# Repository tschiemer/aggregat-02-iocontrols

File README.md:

# aggregat 02 IOControls PCB

User interface peripheral board.

For project info see: https://gitlab.zhdk.ch/aggregat-02/a01-firmware

https://gitlab.zhdk.ch/aggregat-02/a01-pcb-iocontrols

## License

This work is licensed under a Creative Commons Attribution 4.0 International License (CC BY 4.0)

## Revisions

### v1.2

- Replaced small footprint molex connectors with regular 1.00" pin headers.

### v1.1

- fixed not connected 3V3 between DIP switches
- fixed not connected button to GPIO line
- **BREAKING CHANGE** corrected CN3 connector pin assignment to fit with NUCLEO out connector (also see schematics)

## Bill of Materials

Number | Item | Cost per (10/100) Unit(s)  | Cost
--- | --- | --- | ---
1 | PCB Prototype (https://www.pcbway.com/) | 25.00* (10) | 2.50
1 | [DIP Switch SPST 8 Through Hole](https://www.digikey.ch/product-detail/en/78B08ST/GH7192-ND/726250) | 1.26 | 1.26
2 | [DIP Switch SPST 4 Through Hole](https://www.digikey.ch/product-detail/en/78B04T/GH7185-ND/726243) | 1.06 | 2.12
1 | 1 Pin header | |
1 | 2 Pin header 1.00" |  |
2 | 15 Pin header 1.00" |  |
8 | [SMD Res 270Ohm 1% 1/8W 0805 (2012 Metric)](https://www.digikey.ch/product-detail/en/CR0805-FX-2700ELF/118-CR0805-FX-2700ELFCT-ND/10673809) | 2.67 (100) | < 1.00
19 | [SMD Res 330Ohm 1% 1/8W 0805 (2012 Metric)](https://www.digikey.ch/product-detail/en/CRG0805F330R/A106061CT-ND/3477707) | 1.82 (100) | < 1.00
8 | [SMD Res 47kOhm 1% 1/8W 0805 (2012 Metric)](https://www.digikey.ch/product-detail/en/RC0805FR-0747KL/311-47.0KCRCT-ND/730920) |  1.49 (100) | < 1.00
27 | [SMD Res 100kOhm 1% 1/8W 0805 (2012 Metric)](https://www.digikey.ch/product-detail/en/RC0805FR-07100KL/311-100KCRCT-ND/730491) |  1.49 (100) | < 1.00
19| [SMD Cap 0.1uF 10% 6.3V 0805 (2012 Metric)](https://www.digikey.ch/product-detail/en/C0805C104K9RACTU/399-9155-6-ND/3523226) | 7.65 (100) | < 1.00
8 | [Bipolar (BJT) Transistor NPN 40V 800mA SOT-23-3](https://www.digikey.ch/product-detail/en/BSR14/BSR14CT-ND/965560) | 7.37 (100) | < 1.00
4 | Tactile switches |
8 | LEDs ~2 20mA | | ~2.00

* Delivery (~25.00) not included

Total material cost ~< 20.-

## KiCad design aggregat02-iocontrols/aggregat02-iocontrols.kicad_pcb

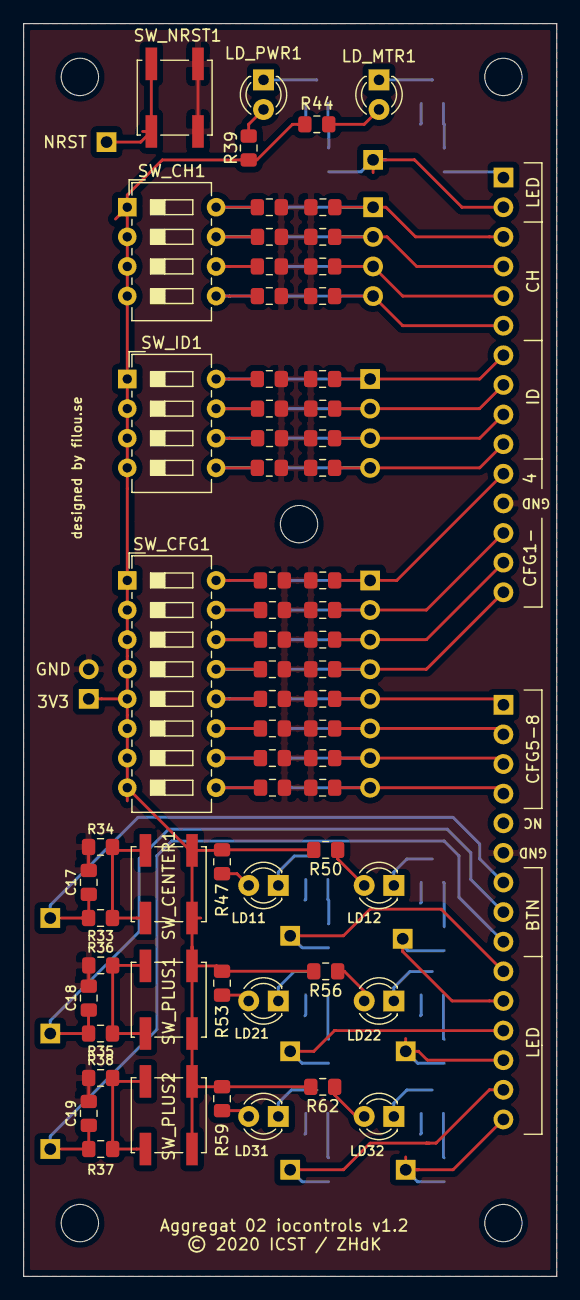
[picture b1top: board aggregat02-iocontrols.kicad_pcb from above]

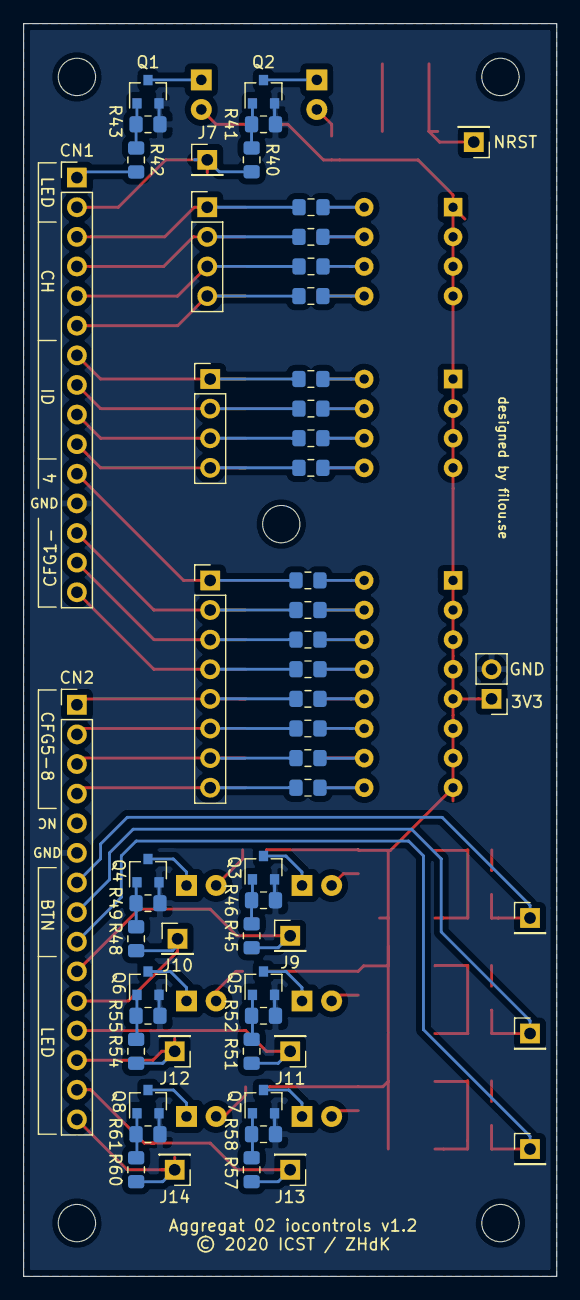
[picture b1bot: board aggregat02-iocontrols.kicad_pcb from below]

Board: 2 copper layers, 45.7 x 107.4 mm, 121 parts (57 on the bottom side), 73 nets.

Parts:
C1, C2, C3, C4, C5, C6, C7, C8, C9, C10, C11, C12, C13, C14, C15, C16, C17, C18, C19: C 0.1u 10% 6V3; C_0805_2012Metric_Pad1.15x1.40mm_HandSolder
CN1, CN2: Conn_01x15; PinHeader_1x15_P2.54mm_Vertical
J1, J2: Conn_01x04; PinHeader_1x04_P2.54mm_Vertical
J3: Conn_01x08; PinHeader_1x08_P2.54mm_Vertical
J4, J5, J6, J7, J9, J10, J11, J12, J13, J14: Conn_01x01; PinHeader_1x01_P2.54mm_Vertical
J17: Conn_01x03; PinHeader_1x02_P2.54mm_Vertical
LD11, LD12, LD21, LD22, LD31, LD32: LED; LED_D3.0mm
LD_MTR1: LED; LED_D3.0mm
LD_PWR1: LED; LED_D3.0mm
NRST: Conn_01x01; PinHeader_1x01_P2.54mm_Vertical
Q1, Q2, Q3, Q4, Q5, Q6, Q7, Q8: Q_NPN_BEC; SOT-23
R1, R3, R5, R7, R9, R11, R13, R15, R17, R19, R21, R23, R25, R27, R29, R31, R33, R35, R37: R 330 1% 1/8; R_0805_2012Metric_Pad1.15x1.40mm_HandSolder
R2, R4, R6, R8, R10, R12, R14, R16, R18, R20, R22, R24, R26, R28, R30, R32, R34, R36, R38, R41, R43, R46, R49, R52, R55, R58, R61: R 100k 1% 1/8; R_0805_2012Metric_Pad1.15x1.40mm_HandSolder
R39, R44, R47, R50, R53, R56, R59, R62: R 270 1% 1/8; R_0805_2012Metric_Pad1.15x1.40mm_HandSolder
R40, R42, R45, R48, R51, R54, R57, R60: R 47k 1% 1/8; R_0805_2012Metric_Pad1.15x1.40mm_HandSolder
SW_CENTER1: SW_Push_Dual; SW_Push_1P1T_NO_CK_KSC6xxJ
SW_CFG1: SW_DIP_x08; SW_DIP_SPSTx08_Slide_6.7x21.88mm_W7.62mm_P2.54mm_LowProfile
SW_CH1: SW_DIP_x04; SW_DIP_SPSTx04_Slide_6.7x11.72mm_W7.62mm_P2.54mm_LowProfile
SW_ID1: SW_DIP_x04; SW_DIP_SPSTx04_Slide_6.7x11.72mm_W7.62mm_P2.54mm_LowProfile
SW_NRST1: SW_Push_Dual; SW_Push_1P1T_NO_CK_KSC6xxJ
SW_PLUS1, SW_PLUS2: SW_Push_Dual; SW_Push_1P1T_NO_CK_KSC6xxJ

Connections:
+3V3: J17.1, R39.2, R44.2, R47.2, R50.2, R53.2, R56.2, R59.2, R62.2, SW_CENTER1.1, SW_CFG1.1, SW_CFG1.2, SW_CFG1.3, SW_CFG1.4, SW_CFG1.5, SW_CFG1.6, SW_CFG1.7, SW_CFG1.8, SW_CH1.1, SW_CH1.2, SW_CH1.3, SW_CH1.4, SW_ID1.1, SW_ID1.2, SW_ID1.3, SW_ID1.4, SW_PLUS1.1, SW_PLUS2.1
CFG_1: R1.2, R2.2, SW_CFG1.16
CFG_2: R9.2, R10.2, SW_CFG1.15
CFG_3: R3.2, R4.2, SW_CFG1.14
CFG_4: R11.2, R12.2, SW_CFG1.13
CFG_5: R5.2, R6.2, SW_CFG1.12
CFG_6: R13.2, R14.2, SW_CFG1.11
CFG_7: R7.2, R8.2, SW_CFG1.10
CFG_8: R15.2, R16.2, SW_CFG1.9
CH_1: R25.2, R26.2, SW_CH1.8
CH_2: R29.2, R30.2, SW_CH1.7
CH_3: R27.2, R28.2, SW_CH1.6
CH_4: R31.2, R32.2, SW_CH1.5
GNDREF: C1.2, C2.2, C3.2, C4.2, C5.2, C6.2, C7.2, C8.2, C9.2, C10.2, C11.2, C12.2, C13.2, C14.2, C15.2, C16.2, C17.2, C18.2, C19.2, CN1.12, CN2.6, J17.2, Q1.2, Q2.2, Q3.2, Q4.2, Q5.2, Q6.2, Q7.2, Q8.2, R2.1, R4.1, R6.1, R8.1, R10.1, R12.1, R14.1, R16.1, R18.1, R20.1, R22.1, R24.1, R26.1, R28.1, R30.1, R32.1, R34.1, R36.1, R38.1, R41.2, R43.2, R46.2, R49.2, R52.2, R55.2, R58.2, R61.2, SW_NRST1.1
ID_1: R17.2, R18.2, SW_ID1.8
ID_2: R21.2, R22.2, SW_ID1.7
ID_3: R19.2, R20.2, SW_ID1.6
ID_4: R23.2, R24.2, SW_ID1.5
LED11: CN2.10, J9.1, R45.2
LED12: CN2.11, J10.1, R48.2
LED21: CN2.12, J11.1, R51.2
LED22: CN2.13, J12.1, R54.2
LED31: CN2.14, J13.1, R57.2
LED32: CN2.15, J14.1, R60.2
LED_MOTOR: CN1.1, R42.2
LED_PWR: CN1.2, J7.1, R40.2
unnamed: LD11.1, Q3.3
unnamed: LD11.2, R47.1
unnamed: LD12.1, Q4.3
unnamed: LD12.2, R50.1
unnamed: LD21.1, Q5.3
unnamed: LD21.2, R53.1
unnamed: LD22.1, Q6.3
unnamed: LD22.2, R56.1
unnamed: LD31.1, Q7.3
unnamed: LD31.2, R59.1
unnamed: LD32.1, Q8.3
unnamed: LD32.2, R62.1
unnamed: LD_MTR1.1, Q1.3
unnamed: LD_MTR1.2, R44.1
unnamed: LD_PWR1.1, Q2.3
unnamed: LD_PWR1.2, R39.1
unnamed: Q1.1, R42.1, R43.1
unnamed: Q2.1, R40.1, R41.1
unnamed: Q3.1, R45.1, R46.1
unnamed: Q4.1, R48.1, R49.1
unnamed: Q5.1, R51.1, R52.1
unnamed: Q6.1, R54.1, R55.1
unnamed: Q7.1, R57.1, R58.1
unnamed: Q8.1, R60.1, R61.1
unnamed: R33.2, R34.2, SW_CENTER1.2
unnamed: R35.2, R36.2, SW_PLUS1.2
unnamed: R37.2, R38.2, SW_PLUS2.2
SW_CENTER: C17.1, CN2.7, J4.1, R33.1
SW_CFG_1: C1.1, CN1.11, J3.1, R1.1
SW_CFG_2: C5.1, CN1.13, J3.2, R9.1
SW_CFG_3: C2.1, CN1.14, J3.3, R3.1
SW_CFG_4: C6.1, CN1.15, J3.4, R11.1
SW_CFG_5: C3.1, CN2.1, J3.5, R5.1
SW_CFG_6: C7.1, CN2.2, J3.6, R13.1
SW_CFG_7: C4.1, CN2.3, J3.7, R7.1
SW_CFG_8: C8.1, CN2.4, J3.8, R15.1
SW_CH_1: C13.1, CN1.3, J2.1, R25.1
SW_CH_2: C15.1, CN1.4, J2.2, R29.1
SW_CH_3: C14.1, CN1.5, J2.3, R27.1
SW_CH_4: C16.1, CN1.6, J2.4, R31.1
SW_ID_1: C9.1, CN1.7, J1.1, R17.1
SW_ID_2: C11.1, CN1.8, J1.2, R21.1
SW_ID_3: C10.1, CN1.9, J1.3, R19.1
SW_ID_4: C12.1, CN1.10, J1.4, R23.1
SW_NRST: NRST.1, SW_NRST1.2
SW_PLUS1: C18.1, CN2.8, J5.1, R35.1
SW_PLUS2: C19.1, CN2.9, J6.1, R37.1

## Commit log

2020-07-15 readme
2020-07-16 v1.0"
2020-07-16 removed backup/cache files
2020-07-23 gitignore and bugfix (non-connected 3V3)
2020-07-24 schematic + assembly help
2020-07-24 fixes
2020-07-24 updated schematics
2020-07-24 physical dimensions
2020-07-24 assembly helpers
2020-07-24 readme update: revisions
2020-08-05 v1.2
2020-08-19 dimensions
2020-11-13 added license
2020-11-13 last updates+doc
2020-11-13 latest gerber files
2020-11-13 changes v1.2

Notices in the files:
aggregat02-iocontrols/aggregat02-iocontrols.kicad_pcb:
© 2020 ICST / ZHdK
